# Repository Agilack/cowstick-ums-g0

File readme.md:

Cowstick UMS
============

The goal of this usb-key is to offer a versatile and customisable mass storage
device. It is *not* desined for very large storage capacity or high throughput
but offer a simple solution to create a storage device with custom features.
This device is part of cowstick boards family.

CAD sources
-----------

This board has been designed using KiCad EDA (version 6). All sources files
(schematics, routing, ...) are available into the `hardware` folder.

<table>
<tr>
<td></td>
<td></td>
</tr><tr>
<td>Fig1: Preview of the KiCad schematics</td>
<td>Fig2: Preview of the KiCad routing</td>
</tr>
</table>

License
-------

This project is OpenHardware. The hardware stuff is published under terms of
the Creative Commons ShareAlike license (CC-by-SA) see [hardware/License.md](hardware/License.md).
The embedded firmware is published under terms of the GNU Lesser General Public
License (LGPL) version 3 see [firmware/License.md](firmware/License.md).

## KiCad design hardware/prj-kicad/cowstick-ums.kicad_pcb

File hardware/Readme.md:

Cowstick UMS - Hardware
=======================

A new revision (rev2) have been designed to include some improvements.

List of changes since previous version :
 - Modify power supply to use another regulator ic (see [test_mt3410.md](test_mt3410.md) )
 - Remove the alternative power supply (LDO, never used)
 - Add a second LED indicator and a user push-button
 - Modify the USB connector (for test)

<table>
<tr>
<td></td>
<td></td>
</tr><tr>
<td>Fig1: 3D view of the top side</td>
<td>Fig2: 3D view of the bottom side</td>
</tr>
</table>

Revision 1
----------

Below pictures of the first revision of the board. Everything works fine, this
revision can still been used.

<table>
<tr>
<td></td>
<td></td>
</tr><tr>
<td>Fig3: cowstick-ums revision 1</td>
<td>Fig4: Preview of rev1 routing</td>
</tr>
<tr>
<td></td>
<td></td>
</tr><tr>
<td>Fig5: 3D view of the top side</td>
<td>Fig6: 3D view of the bottom side</td>
</tr>
</table>

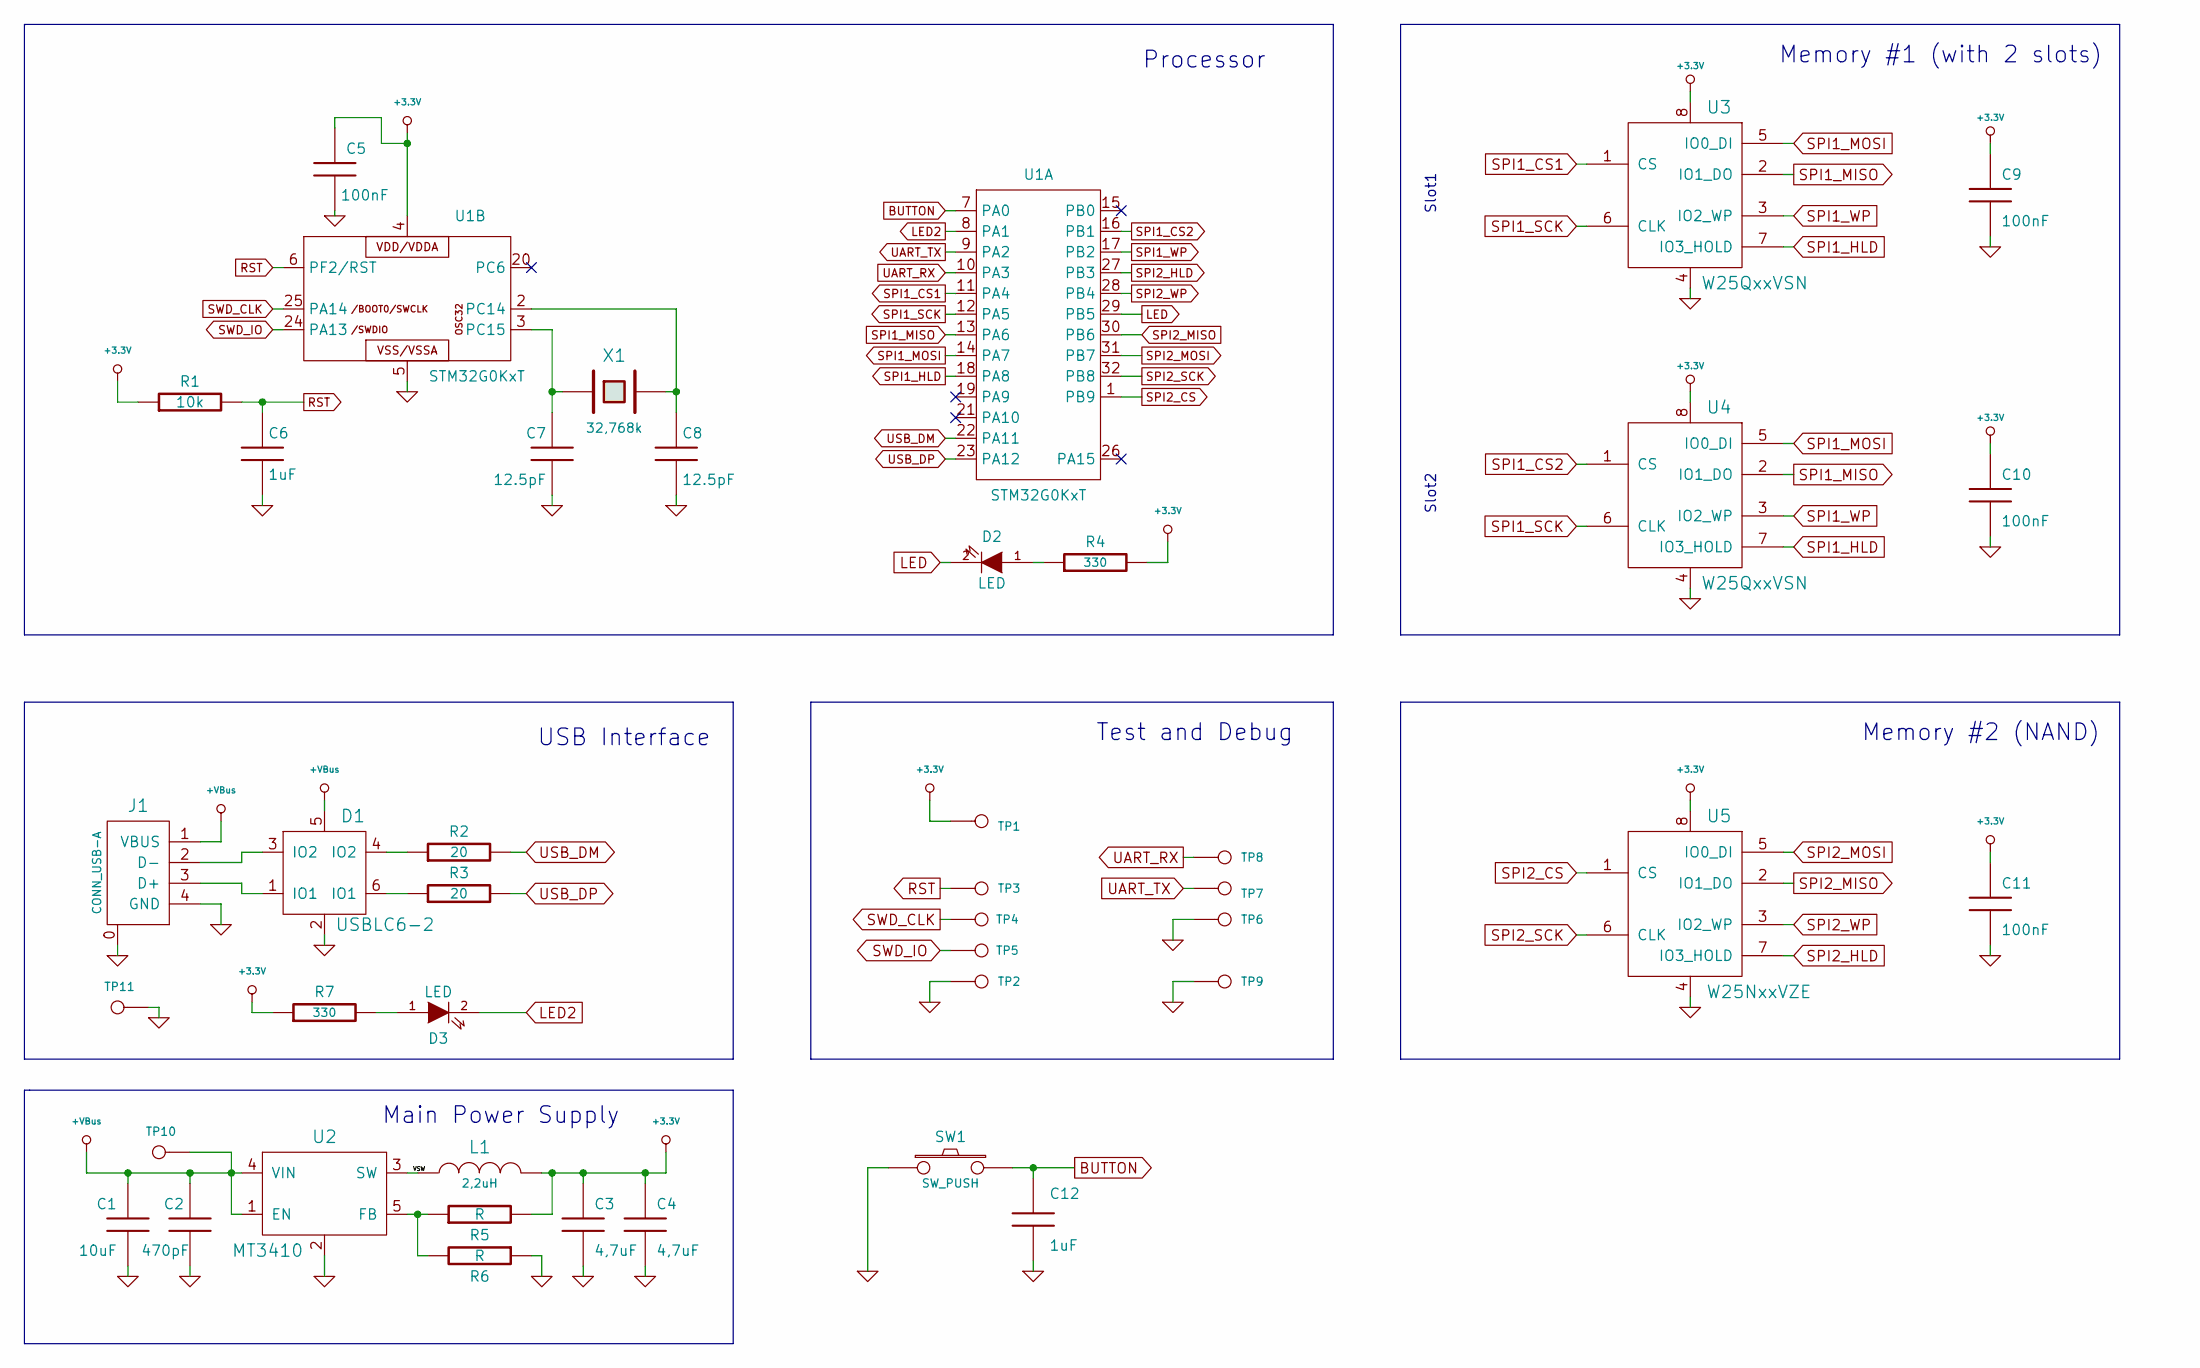
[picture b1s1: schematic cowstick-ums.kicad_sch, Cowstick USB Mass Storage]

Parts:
C1: 10uF; C_0805
C2: 470pF; C_0603
C3, C4: 4,7uF; C_0805
C5, C9, C10, C11: 100nF; C_0603
C6, C12: 1uF; C_0603
C7, C8: 12.5pF; C_0603
D1: USBLC6-2; SOT23-6
D2, D3: LED; C_0805
J1: CONN_USB-A; CONN_AM90YC
L1: 2,2uH; I_SMD_3x3
R1: 10k; R_0603
R2, R3: 20; R_0603
R4, R7: 330; R_0603
R5, R6: R; R_0603
SW1: SW_PUSH; BUT_TC029
TP1: CONN_1; TP_SMD2
TP2, TP3, TP4, TP5, TP7, TP8, TP10, TP11: CONN_1; TP_SMD
TP6, TP9: CONN_1; TP_PIN
U1: STM32G0KxT; TQFP32
U2: MT3410; SOT23-5
U3, U4: W25QxxVSN; SOIC-8
U5: W25NxxVZE; WSON8
X1: 32,768k; Q_3.2x1.5

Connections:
+3.3V: C3.1, C4.1, C5.1, C9.1, C10.1, C11.1, L1.2, R1.1, R4.2, R5.2, R7.1, TP1.1, U1.4, U3.8, U4.8, U5.8
+VBus: C1.1, C2.1, D1.5, J1.1 (VBUS), TP10.1, U2.1 (EN), U2.4 (VIN)
/VSW: L1.1, U2.3 (SW)
BUTTON: C12.1, SW1.2, U1.7 (PA0)
GND: C1.2, C2.2, C3.2, C4.2, C5.2, C6.2, C7.2, C8.2, C9.2, C10.2, C11.2, C12.2, D1.2, J1.0, J1.4 (GND), R6.1, SW1.1, TP2.1, TP6.1, TP9.1, TP11.1, U1.5, U2.2, U3.4, U4.4, U5.4
LED: D2.2 (K), U1.29 (PB5)
LED2: D3.2 (K), U1.8 (PA1)
unnamed: C7.1, U1.3 (PC15), X1.1
unnamed: C8.1, U1.2 (PC14), X1.2
unnamed: D1.1 (IO1), J1.3 (D+)
unnamed: D1.3 (IO2), J1.2 (D-)
unnamed: D1.4 (IO2), R2.1
unnamed: D1.6 (IO1), R3.1
unnamed: D2.1 (A), R4.1
unnamed: D3.1 (A), R7.2
unnamed: R5.1, R6.2, U2.5 (FB)
RST: C6.1, R1.2, TP3.1, U1.6 (PF2/RST)
SPI1_CS1: U1.11 (PA4), U3.1 (CS)
SPI1_CS2: U1.16 (PB1), U4.1 (CS)
SPI1_HLD: U1.18 (PA8), U3.7 (IO3_HOLD), U4.7 (IO3_HOLD)
SPI1_MISO: U1.13 (PA6), U3.2 (IO1_DO), U4.2 (IO1_DO)
SPI1_MOSI: U1.14 (PA7), U3.5 (IO0_DI), U4.5 (IO0_DI)
SPI1_SCK: U1.12 (PA5), U3.6 (CLK), U4.6 (CLK)
SPI1_WP: U1.17 (PB2), U3.3 (IO2_WP), U4.3 (IO2_WP)
SPI2_CS: U1.1 (PB9), U5.1 (CS)
SPI2_HLD: U1.27 (PB3), U5.7 (IO3_HOLD)
SPI2_MISO: U1.30 (PB6), U5.2 (IO1_DO)
SPI2_MOSI: U1.31 (PB7), U5.5 (IO0_DI)
SPI2_SCK: U1.32 (PB8), U5.6 (CLK)
SPI2_WP: U1.28 (PB4), U5.3 (IO2_WP)
SWD_CLK: TP4.1, U1.25 (PA14)
SWD_IO: TP5.1, U1.24 (PA13)
UART_RX: TP8.1, U1.10 (PA3)
UART_TX: TP7.1, U1.9 (PA2)
USB_DM: R2.2, U1.22 (PA11)
USB_DP: R3.2, U1.23 (PA12)

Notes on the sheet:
Memory #2 (NAND)
Memory #1 (with 2 slots)
Test and Debug
Slot1
Slot2
Main Power Supply
Processor
USB Interface

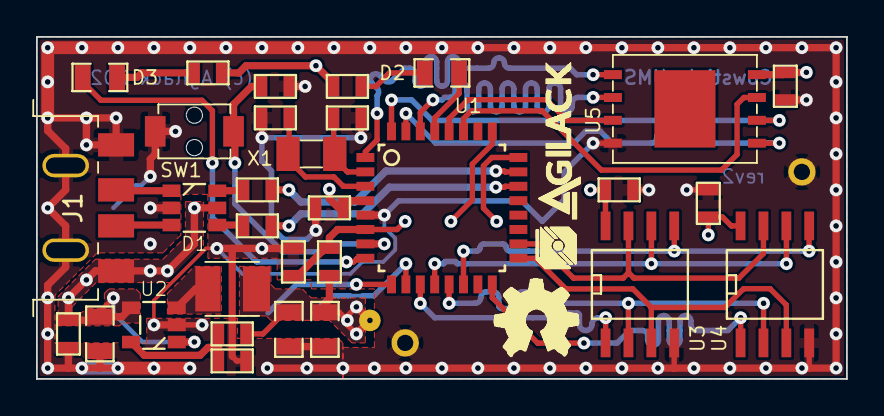
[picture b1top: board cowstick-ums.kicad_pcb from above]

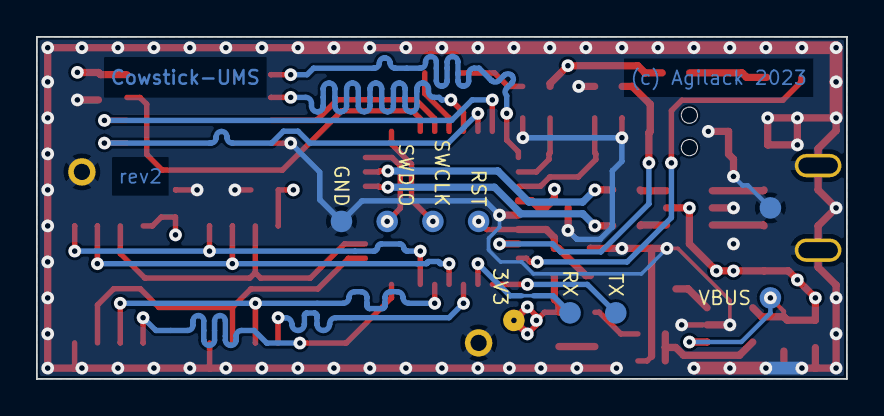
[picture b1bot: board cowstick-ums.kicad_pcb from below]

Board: 4 copper layers, 45.0 x 19.0 mm, 44 parts (8 on the bottom side), 36 nets.

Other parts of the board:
agilack-11.5: 450px; logo-agilack-11.5
ohw_logo: VAL**; logo-ohw

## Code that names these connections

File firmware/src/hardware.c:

/**
 * @file  hardware.c
 * @brief Low-level cowstick-ums hardware configuration
 *
 * @author Saint-Genest Gwenael <gwen@cowlab.fr>
 * @copyright Agilack (c) 2023
 *
 * @page License
 * Cowstick-UMS firmware is free software: you can redistribute it and/or
 * modify it under the terms of the GNU Lesser General Public License
 * version 3 as published by the Free Software Foundation. You should have
 * received a copy of the GNU Lesser General Public License along with this
 * program, see LICENSE.md file for more details.
 * This program is distributed WITHOUT ANY WARRANTY.
 */
#include "hardware.h"

static inline void _init_clocks(void);
static inline void _init_led(void);
static inline void _init_spi(void);
static inline void _init_uart(void);
static inline void _init_usb(void);

/**
 * @brief Initialize processor, clocks and some peripherals
 *
 * This function should be called on startup for clocks and IOs configuration.
 */
void hw_init(void)
{
	int i;

	/* RCC : Activate GPIOA and GPIOB */
	reg_wr(RCC_IOPENR, (1 << 1) | (1 << 0));
	/* RCC : Reset GPIOA and GPIOB */
	reg_wr(RCC_IOPRSTR, (1 << 1) | (1 << 0));
	for (i = 0; i < 16; i++)
		asm volatile("nop");
	reg_wr(RCC_IOPRSTR, 0);

	_init_clocks();

	_init_led();
	_init_uart();
	_init_spi();
	_init_usb();
}

/**
 * @brief Configure clocks for main speed operations
 *
 * The clocks are configured as is:
 *   - Processor and SYSCLK run at 64 MHz (using HSI16 and PLL)
 *   - The debug port (USART2) use HSI16
 *   - USB device controller use internal RC oscillator HSI48
 *   - An optional low speed clock for RTC using LSE
 */
static inline void _init_clocks(void)
{
	u32 val;

	/* Set HSI16 as USART2 clock source */
	val = reg_rd(RCC_CCIPR);
	val &= ~(u32)(3 << 2);
	val |=  (u32)(2 << 2);
	reg_wr(RCC_CCIPR, val);

	/* If PLL is used, SYSCLK = 64MHz else SYSCLK = 16 MHz */
#ifdef USE_PLL
	/* Configure PLL */
	val =  (2 << 0);    // PLL clock source = HSI16
	val |= (1 << 4);    // set M (VCO divisor) VCO clock input = 8MHz
	val |= (16 <<  8);  // set N (VCO multiplier) VCO output = 128MHz
	val |= ( 1 << 29);  // set R output divisor, PLLRCLK output = 64MHz
	reg_wr(RCC_PLL_CFGR, val);
	/* Activate PLL and wait for PLL ready */
	reg_set(RCC_CR, (1 << 24));
	while( (reg_rd(RCC_CR) & (1 << 25)) == 0)
		;

	/* Set Flash latency to 2WS */
	reg_set((u32)(FLASH + 0x00), 2); // Flash ACR
	while( (reg_rd(FLASH + 0x00) & 7) != 2)
		;

	/* Enable PLLRCLK */
	reg_set(RCC_PLL_CFGR, (1 << 28));

	/* Change the clock source */
	val  = reg_rd(RCC_CFGR);
	val &= ~(u32)0x07; // Clear System Clock Switch
	val |=  (u32)0x02; // Set PLLRCLK
	reg_wr(RCC_CFGR, val);
#endif

	/* Activate HSI48 RC oscillator */
	reg_set(RCC_CR, (1 << 22));
	while( (reg_rd(RCC_CR) & (1 << 23)) == 0)
		;
	/* Activate CRS */
	reg_set((u32)RCC_APBENR1, (1 << 16));
	/* Reset CRS */
	reg_set((u32)RCC_APBRSTR1, (1 << 16));
	(void)reg_rd((u32)RCC_APBRSTR1);
	reg_clr((u32)RCC_APBRSTR1, (1 << 16));
	/* Configure CRS */
	val = (2 << 28); // SYNC_SRC: USB SOF
	val |= (47999 & 0xFFFF); // Reload value
	val |= ( 22 << 16); // FELIM
	reg_wr(CRS+0x04, val); // CRS_CFGR
	/* Adjust TRIM */
	val = reg_rd(CRS+0x00);
	val &= ~(u32)(0x7F << 8);
	val |=  (u32)(32   << 8);
	reg_wr(CRS+0x00, val);
	/* Enable Auto-Trim and Error counter*/
	reg_set(CRS+0x00, (1 << 6) | (1 << 5));

#ifdef USE_LSE
	/* Activate power controller (PWR) */
	reg_set(RCC_APBENR1, (1 << 28));
	/* Disable RTC domain write protection */
	reg_set(PWR + 0x00, (1 << 8));
	/* Configure LSE drive level */
	reg_set(RCC_BDCR, (3 << 3));
	/* Activate LSE (set LSEON bit) */
	reg_set(RCC_BDCR, (1 << 0));
	for (i = 0; i < 0x100000; i++)
	{
		if (reg_rd(RCC_BDCR) & (1 << 1))
			break;
	}
#endif
}

/**
 * @brief Initialize the IO connected to LED
 *
 */
static inline void _init_led(void)
{
	u32 v;

	/* Use open-drain io for LED */
	reg_wr(GPIO_OTYPER(GPIOB), (1 << 5));
	/* Default state : IO=1 -> LED off */
	reg_wr(GPIO_BSRR(GPIOB),   (1 << 5));
	/* Set PB5 as general purpose output */
	v = reg_rd(GPIO_MODER(GPIOB));
	v &= ~(u32)(3 << 10);
	v |=  (u32)(1 << 10);
	reg_wr(GPIO_MODER(GPIOB), v);
}

/**
 * @brief Initialize the IOs connected to SPI memories
 *
 */
static inline void _init_spi(void)
{
	u32 moder_a, moder_b;
	u32 afrl_a,  afrl_b, afrh_b;
	u32 speed_a, speed_b;

	/* Read all registers that will be modified for SPI ios */
	moder_a = reg_rd(GPIO_MODER(GPIOA));
	moder_b = reg_rd(GPIO_MODER(GPIOB));
	afrl_a  = reg_rd(GPIO_AFRL(GPIOA));
	afrl_b  = reg_rd(GPIO_AFRL(GPIOB));
	afrh_b  = reg_rd(GPIO_AFRH(GPIOB));
	speed_a = reg_rd(GPIO_OSPEEDR(GPIOA));
	speed_b = reg_rd(GPIO_OSPEEDR(GPIOB));

	/* SPI1: Configure Chip Select 1 (PA4) as output */
	reg_wr(GPIO_BSRR(GPIOA), (1 << 4));
	moder_a &= ~(u32)(3 << 8);
	moder_a |=  (u32)(1 << 8);
	/* SPI1: Configure Chip Select 2 (PB1) as output */
	reg_wr(GPIO_BSRR(GPIOB), (1 << 1));
	moder_b &= ~(u32)(3 << 2);
	moder_b |=  (u32)(1 << 2);
	/* SPI2: Configure Chip Select (PB9) as output */
	reg_wr(GPIO_BSRR(GPIOB), (1 << 9));
	moder_b &= ~(u32)(3 << 18);
	moder_b |=  (u32)(1 << 18);
	/* Apply MODER now to force all memory chips to inactive (CS=1) */
	reg_wr(GPIO_MODER(GPIOA), moder_a);
	reg_wr(GPIO_MODER(GPIOB), moder_b);

	/* SPI1: Configure SCK signal (use AF) */
	afrl_a &= ~(u32)(0xF << 20); // Reset PA5 AF to AF0
	moder_a &= ~(u32)(3 << 10);  // Clear PA5 mode
	moder_a |=  (u32)(2 << 10);  // Set mode to Alternate Function
	speed_a |=  (u32)(3 << 10);  // Very High Speed
	/* SPI1: Configure MISO signal (use AF) */
	afrl_a &= ~(u32)(0xF << 24); // Reset PA6 AF to AF0
	moder_a &= ~(u32)(3 << 12);  // Clear PA6 mode
	moder_a |=  (u32)(2 << 12);  // Set mode to Alternate Function
	speed_a |=  (u32)(3 << 12);  // Very High Speed
	/* SPI1: Configure MOSI signal (use AF) */
	afrl_a &= ~(u32)(0xF << 28); // Reset PA7 AF to AF0
	moder_a &= ~(u32)(3 << 14);
	moder_a |=  (u32)(2 << 14);  // Set PA7 mode to Alternate Function
	speed_a |=  (u32)(3 << 14);  // Very High Speed
	/* SPI1: Congigure Hold signal (as GPIO) */
	reg_wr(GPIO_BSRR(GPIOA), (1 << 24));
	moder_a &= ~(u32)(3 << 16);
	moder_a |=  (u32)(1 << 16);  // Set PA8 mode to GP output
	/* SPI1: Configure Write Protect signal (as GPIO) */
	reg_wr(GPIO_BSRR(GPIOB), (1 << 18)); // WP=0 (proction active)
	moder_b &= ~(u32)(3 << 4);
	moder_b |=  (u32)(1 << 4);   // Set PB2 mode to GP output

	/* SPI2: Configure SCK signal (use AF) */
	afrh_b &= ~(u32)(0xF << 0);
	afrh_b |=  (u32)(  1 << 0); // PB8 use AF1
	moder_b &= ~(u32)(3 << 16);
	moder_b |=  (u32)(2 << 16); // Set PB8 mode to Alternate Function
	speed_b |=  (u32)(3 << 16); // Very High Speed
	/* SPI2: Configure MISO signal (use AF) */
	afrl_b &= ~(u32)(0xF << 24);
	afrl_b |=  (u32)(  4 << 24); // PB6 use AF4 (SPI2_MISO)
	moder_b &= ~(u32)(3 << 12);
	moder_b |=  (u32)(2 << 12);  // Set PB6 mode to Alternate Function
	speed_b |=  (u32)(3 << 12);  // Very High Speed
	/* SPI2: Configure MOSI signal (use AF) */
	afrl_b &= ~(u32)(0xF << 28);
	afrl_b |=  (u32)(  1 << 28); // PB7 use AF1 (SPI2_MOSI)
	moder_b &= ~(u32)(3 << 14);
	moder_b |=  (u32)(2 << 14);  // Set PB7 mode to Alternate Function
	speed_b |=  (u32)(3 << 14);  // Very High Speed
	/* SPI2: Configure Hold signal (as GPIO) */
	reg_wr(GPIO_BSRR(GPIOB), (1 << 19)); // WP=0 (proction active)
	moder_b &= ~(u32)(3 << 6);
	moder_b |=  (u32)(1 << 6);  // Set PB3 mode to GP output
	/* SPI2: Configure Write Protect signal (as GPIO) */
	reg_wr(GPIO_BSRR(GPIOB), (1 << 20));
	moder_b &= ~(u32)(3 << 8);
	moder_b |=  (u32)(1 << 8);  // Set PB4 mode to GP output

	/* Apply all registers changes */
	reg_wr(GPIO_AFRL(GPIOA), afrl_a);
	reg_wr(GPIO_AFRL(GPIOB), afrl_b);
	reg_wr(GPIO_AFRH(GPIOB), afrh_b);
	reg_wr(GPIO_OSPEEDR(GPIOA), speed_a);
	reg_wr(GPIO_OSPEEDR(GPIOB), speed_b);
	reg_wr(GPIO_MODER(GPIOA), moder_a);
	reg_wr(GPIO_MODER(GPIOB), moder_b);
}

/**
 * @brief Initialize IOs of the (debug) uart port
 *
 */
static inline void _init_uart(void)
{
	u32 v;

	/* Configure PA2 (UART-TX) and PA3 (UART-RX) to use AF1 (USART2) */
	v = reg_rd(GPIO_AFRL(GPIOA));
	v &= ~(u32)(0xF <<  8); // Clear current PA2 config
	v |=  (u32)(  1 <<  8); // PA2 use AF1
	v &= ~(u32)(0xF << 12); // Clear current PA3 config
	v |=  (u32)(  1 << 12); // PA3 use AF1
	reg_wr(GPIO_AFRL(GPIOA), v);

	/* Configure PA2 and PA3 to use alternate function */
	v = reg_rd(GPIO_MODER(GPIOA));
	v &= ~(u32)( (3 << 4) | (3 << 6) );
	v |=  (u32)( (2 << 4) | (2 << 6) );
	reg_wr(GPIO_MODER(GPIOA), v);
}

static inline void _init_usb(void)
{
	u32 v;

	/* Activate SYSCFG (to use PA11 PA12) */
	reg_set(RCC_APBENR2, (1 << 0));

#ifdef HW_RESTART
	v = reg_rd(RCC_CCIPR2);
	v &= ~(u32)(3 << 12); // 00 = HSI48
	reg_wr(RCC_CCIPR2, v);
#endif
	/* Configure PA11 and PA12 as analog (USB pins use special functions) */
	v = reg_rd(GPIO_MODER(GPIOA));
	v |=  (u32)( (3 << 22) | (3 << 24) );
	reg_wr(GPIO_MODER(GPIOA), v);
}
/* EOF */

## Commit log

2023-02-03 --=={ Create project }==--
2023-02-04 Hardware: Improve PCB r1, add MCU (STM32G0)
2023-02-07 Hardware: Improve PCB r1, add two SOIC8 flash memory ic for channel 1
2023-02-09 Hardware: Improve PCB r1, add one Nand flash memory for "large" capacity (channel 2)
2023-02-11 Hardware: Finish and cleanup pcb r1 and create production files
2023-02-14 Firmware: Create a basic firmware (init hw, uart, and detect memories)
2023-02-16 Firmware: Add clock configuration (PLL and LSE) and scripts for load/debug
2023-02-18 Firmware: Add an abstraction layer "mem" to access (r/w) external memories
2023-02-21 Hardware: Add pictures of rev1, update readme and license
2023-02-22 Firmware: Create a module for USB device interface (Wip ! incomplete enumeration)
2023-02-23 Firmware: Improve USB module, enumeration complete (Wip)
2023-02-24 Firmware: Improve USB module, cleanup endpoint-0 functions
2023-02-25 Firmware: Improve USB module, add missing stardard requests, and add device unit-test
2023-03-18 Firmware: Create a dummy BULK interface driver to test data endpoints support
2023-03-28 Firmware: Improve USB, add interface driver, improve handle of control requests
2023-04-06 Firmware: Insert an USB Mass Storage class driver (basic support, wip)
2023-04-12 Firmware: Improve Mass Storage driver (MSC), all basic features now available
2023-04-14 Firmware: Improve SCSI driver, add more commands and fix access to external flash chip
2023-04-18 Firmware: Improve Mass Storage, add ResetRecovery command and create a unit-test for MSC layer
2023-04-22 Firmware: Improve Mass Storage, handle more errors (test the 13 cases of Bulk-Only Transport spec)
2023-05-02 Hardware: Modify PCB for a new revision (rev2) and create production files - Add pushbutton and a second LED - Replace power reg and USB connector with a new refs
2023-05-09 Firmware: Create a new module to handle relative time and duration (using systick)
2023-05-10 Firmware: Create a new module to handle and dispatch log messages
2023-05-11 Firmware: Improve SCSI layer, add LUN structure and extract read/write functions
2023-05-12 Firmware: Create an API for custom app extension. Add custom app skeleton.
2023-05-13 Firmware: Improve APP extension, expose more functions, improve SCSI to handle vendor requests
2023-05-16 Hardware: Add pictures of rev2, update readme files
2023-05-30 Firmware: Improve SCSI, add function to handle READ BUFFER and WRITE BUFFER (very basically)
2023-05-31 Firmware: Add a new driver for MCU internal flash memory (erase/write)
2023-06-01 Firmware: Move SCSI read/write buffer to dedicated files, add microcode upgrade
